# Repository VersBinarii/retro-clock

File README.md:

# Retro Clock

Nixie clock based on stm32f103 "BluePill"

# Description

Its based on stm32f103 RTC peripheral.
The nixie valves are driven with 74LS145 BCD to decimal decoder
The time is outputed through the NIXIE as wel as through the smal I2C based OLED.

# Operation

Long press 'Ok' putton to enter into edit mode. 
Then short press selects the digit to edit. 'Left' and 'Right' buttons increase/decrease the value.
Long press 'Ok' again to confirm new time.

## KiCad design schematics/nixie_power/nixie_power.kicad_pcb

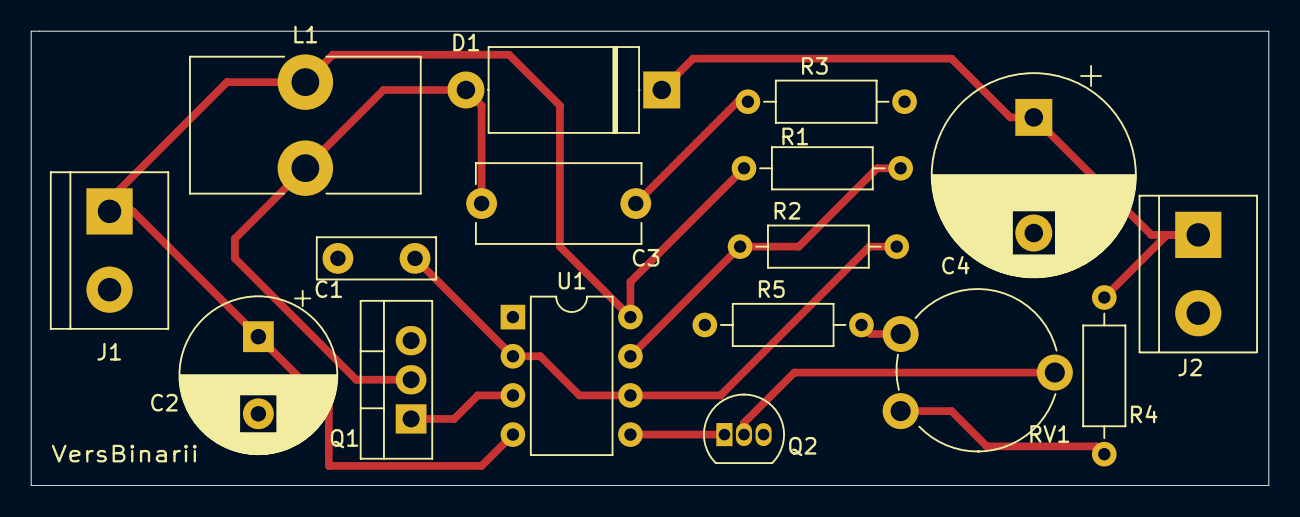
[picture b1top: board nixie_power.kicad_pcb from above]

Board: 2 copper layers, 80.3 x 29.5 mm, 17 parts (0 on the bottom side), 12 nets.

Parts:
C1: 2n2; C_Disc_D7.5mm_W2.5mm_P5.00mm
C2: 470uF/250V; CP_Radial_D10.0mm_P5.00mm
C3: 100p/400V; C_Disc_D10.5mm_W5.0mm_P10.00mm
C4: 15u/350V; CP_Radial_D13.0mm_P7.50mm
D1: 400V/2A; D_DO-27_P12.70mm_Horizontal
J1, J2: Screw_Terminal_01x02; TerminalBlock_bornier-2_P5.08mm
L1: 100mH; L_Toroid_Vertical_L14.7mm_W8.6mm_P5.58mm_Pulse_KM-1
Q1: IRF740; TO-220-3_Vertical
Q2: BC547; TO-92_Inline
R1: 1K; R_Axial_DIN0207_L6.3mm_D2.5mm_P10.16mm_Horizontal
R2: 10K; R_Axial_DIN0207_L6.3mm_D2.5mm_P10.16mm_Horizontal
R3: 47R; R_Axial_DIN0207_L6.3mm_D2.5mm_P10.16mm_Horizontal
R4: 220K; R_Axial_DIN0207_L6.3mm_D2.5mm_P10.16mm_Horizontal
R5: 470; R_Axial_DIN0207_L6.3mm_D2.5mm_P10.16mm_Horizontal
RV1: 1k; Potentiometer_Piher_PT-10-V10_Vertical
U1: NE555P; DIP-8_W7.62mm

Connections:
GND: C1.2, C2.2, C4.2, J1.2, J2.2, Q1.3, Q2.3, R3.2, R5.2, U1.1
unnamed: C1.1, R2.2, U1.2, U1.6
unnamed: C2.1, J1.1, L1.1, R1.1, U1.4, U1.8
unnamed: C3.1, D1.2, L1.2, Q1.2
unnamed: C3.2, R3.1
unnamed: C4.1, D1.1, J2.1, R4.1
unnamed: Q1.1, U1.3
unnamed: Q2.1, U1.5
unnamed: Q2.2, RV1.2
unnamed: R1.2, R2.1, U1.7
unnamed: R4.2, RV1.1
unnamed: R5.1, RV1.3

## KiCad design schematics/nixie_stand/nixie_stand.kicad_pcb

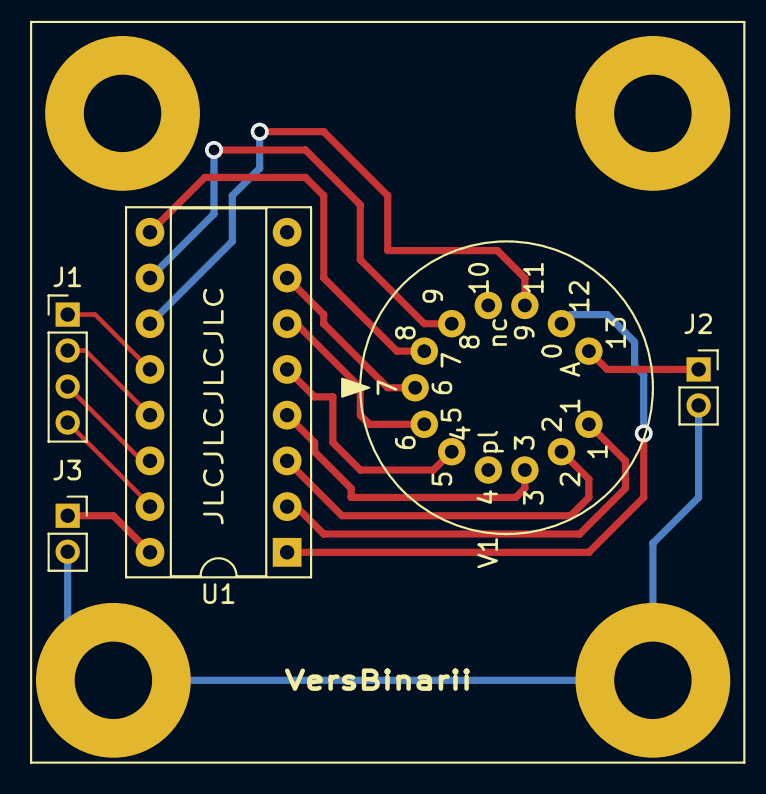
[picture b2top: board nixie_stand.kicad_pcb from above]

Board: 2 copper layers, 9 parts (0 on the bottom side), 17 nets.

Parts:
H1, H2, H3, H4: MountingHole_Pad; MountingHole_4.3mm_M4_Pad
J1: Conn_01x04; PinHeader_1x04_P2.00mm_Vertical
J2, J3: Conn_01x02; PinSocket_1x02_P2.00mm_Vertical
U1: 74LS145; DIP-16_W7.62mm_Socket
V1: Z574M; nixie_z574m

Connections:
+5V: J3.1, U1.16
GND: H1.1, H2.1, H3.1, H4.1, J2.2, J3.2, U1.8
unnamed: J1.1, U1.12
unnamed: J1.2, U1.13
unnamed: J1.3, U1.14
unnamed: J1.4, U1.15
unnamed: U1.1, V1.12
unnamed: U1.2, V1.1
unnamed: U1.3, V1.2
unnamed: U1.4, V1.3
unnamed: U1.5, V1.5
unnamed: U1.6, V1.6
unnamed: U1.7, V1.7
unnamed: U1.9, V1.8
unnamed: U1.10, V1.9
unnamed: U1.11, V1.11
VCC: J2.1, V1.13
